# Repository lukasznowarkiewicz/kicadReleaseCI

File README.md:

# KiCad Release CI

This repository provides:

1. A **Docker-based** environment for running [KiCad 8.x](https://www.kicad.org/) in a CI context.  
2. A **reusable GitHub Actions workflow** (`.github/workflows/kicad_export.yml`) that you can call from your PCB project repos.  
3. A **script** that automatically searches for `.kicad_pcb` (and matching `.kicad_sch`) files, exports manufacturing outputs, and stores them in an `outputs/` folder.

## Table of Contents

- [Intended Use](#intended-use)  
- [Using From Another Repository](#using-from-another-repository)  
- [Development](#development)  
  - [1. Build Docker Image Locally](#1-build-docker-image-locally)  
  - [2. Run the Docker Container](#2-run-the-docker-container)  
  - [3. Modify the Export Script](#3-modify-the-export-script)  
- [What is Exported](#what-is-exported)  
- [License](#license)  

---

## Intended Use

- **Automate** KiCad manufacturing outputs (Gerbers, Drill files, BOM, PDF plots, etc.) for your hardware projects.  
- Keep the CI logic and Docker environment **centralized**.  
- **Reusable** across multiple PCB projects.  
- Fully **headless** KiCad environment, leveraging `kicad-cli` commands in KiCad 8.

---

## Using From Another Repository

### 1) Reference Our Reusable Workflow

In your **KiCad project repository**, create a workflow file (e.g., `.github/workflows/kicad_export_caller.yml`):

```yaml
name: "Kicad 8 release CI"

on:
  push:
    branches: [ "main" ]
  pull_request:
    branches: [ "main" ]
  # or to allow manual triggers:
  # workflow_dispatch:

jobs:
  call-export:
    uses: lukasznowarkiewicz/kicadReleaseCI/.github/workflows/kicad_export.yml@main
    with:
      target_repo: ${{ github.repository }}
      target_ref: ${{ github.ref }}
```

- **`uses:`** points to this repo’s workflow file (`kicad_export.yml`).  
- **`target_repo`** and **`target_ref`** are inputs required by the reusable workflow to know which repo and branch to check out.

### 2) Trigger the Workflow

- Whenever you push to `main` or open a pull request, GitHub Actions calls `kicad_export.yml` from **kicadReleaseCI**, checks out your KiCad files, and runs the export container.  
- The results are uploaded as an artifact named `kicad-outputs`. Download it from the “Actions” tab in your project repo.

> **Note**: If your `kicadReleaseCI` repo is **private**, ensure you have set the right permissions and that both repos are in the same organization (or you have a proper token setup).

---

## Development

If you want to **develop** or **modify** this CI workflow in `kicadReleaseCI`, here are common tasks:

### 1. Build Docker Image Locally

```bash
git clone https://github.com/lukasznowarkiewicz/kicadReleaseCI.git
cd kicadReleaseCI
docker build -t kicad-autogen:latest .
```

This uses the local `Dockerfile`, which installs KiCad 8 and copies the `generate_kicad_outputs.sh` script.

### 2. Run the Docker Container

You can run the image manually, mounting a **KiCad project** folder to `/project`:

```bash
docker run --rm -it -v "$(pwd)":/project -w /project kicad-autogen:latest
```

or optinally run container and enter containers' bash:
```bash
docker run --rm -it \
  --entrypoint bash \
  -v "$(pwd)":/project \
  -w /project \
  kicad-autogen:latest
```

- The container entrypoint calls `generate_kicad_outputs.sh`, which searches `/project` for `.kicad_pcb` files, exports all outputs, and places them into `outputs/` subfolders.
- When the container finishes, check `some_kicad_project/outputs/` on your host system for the results.

### 3. Modify the Export Script

- The **main logic** is in `generate_kicad_outputs.sh`. It does:
  - `find . -type f -name '*.kicad_pcb'` to locate boards in subfolders.
  - If a matching `.kicad_sch` is found, exports schematic PDF & BOM.
  - Exports board PDF, Gerbers, and NC drill files for each PCB.
  - Places everything under a mirrored folder structure in `outputs/<subdirectory>`.
- **Common tweaks**:
  - Change PDF layers (default is `F.Cu,B.Cu,F.SilkS,B.SilkS,Edge.Cuts`).
  - Add or remove exports (e.g. `kicad-cli pcb export svg`).
  - Add optional 3D or advanced BOM scripts.

After changes, **rebuild** the Docker image or push to GitHub so the updated script is used in subsequent CI runs.

---

## What is Exported

By default, the script exports the following for each `.kicad_pcb`:

1. **Board PDF**: A multi-layer PDF of copper layers, silkscreen, and board edges.  
2. **Gerber Files**: For each layer, plus `.gbrjob`.  
3. **NC Drill Files**: Excellon drills (`.drl`, `.map`).  
4. **Schematic PDF & BOM**: If a **matching** `.kicad_sch` (same base name) is found. BOM is exported as `.csv`.

All generated files go into `outputs/<mirroring the original folder structure>`. For instance, if your KiCad board is at `sub/folder/myboard.kicad_pcb`, the outputs go to `outputs/sub/folder/`.

---

## License

This project is published under the [Apache-2.0](LICENSE) license.

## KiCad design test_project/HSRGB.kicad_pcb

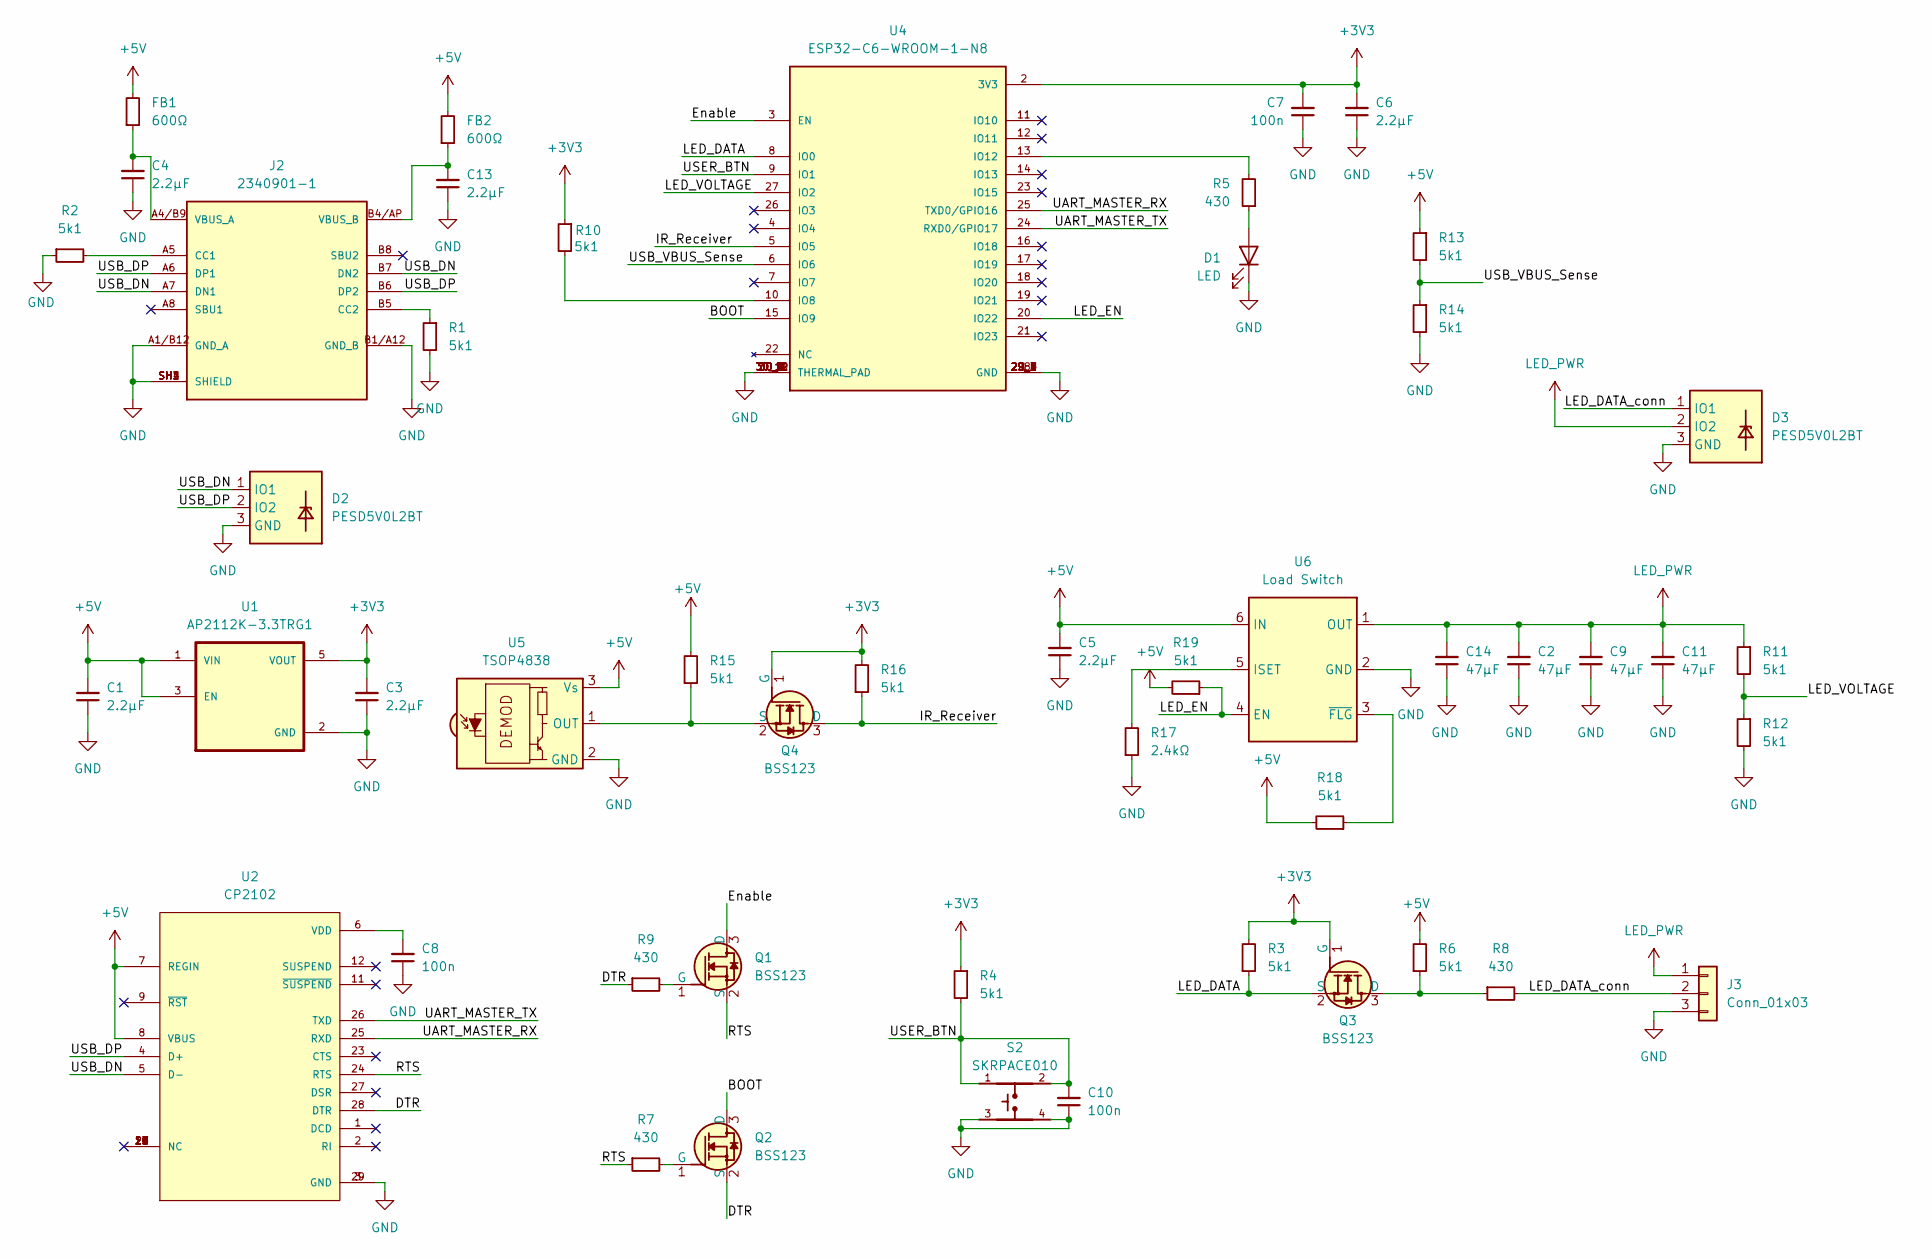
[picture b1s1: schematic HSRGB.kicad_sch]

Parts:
C1, C3, C4, C5, C6, C13: C_2u2_10pct_16V_0402_GRM155R61C225KE11D; C_0402; MPN GRM155R61C225KE11D
C2, C9, C11, C14: C_47u_20pct_10V_0805_CC0805MKX5R6BB476; C_0805; MPN CC0805MKX5R6BB476
C7, C8, C10: C_100n_0402; C_0402; Voltage 10V; MPN GRM155R61A104KE01D
D1: LED; LED_KPT-1608ZGC
D2, D3: PESD5V0L2BT; MPN PESD5V0L2BT
FB1, FB2: FB_600_Ohm_0805; FB_0805_2012Metric; Tolerance ±25%; MPN HCB2012KF-601T15
J2: 2340901-1; PARTREV A
J3: Conn_01x03; 1x03_P2.54mm_LED_pads
Q1, Q2, Q3, Q4: BSS123; SOT-23-3; MPN BSS123
R1, R2, R3, R4, R6, R10, R11, R12, R13, R14, R15, R16, R18, R19: R_5k1_0402; R_0402; Tolerance 5%; MPN AC0402JR-075K1L
R5, R7, R8, R9: R_430_0402; R_0402; Tolerance 1%; MPN RTT024300FTH
R17: R_2k4_1pct_0402_CRCW04022K40FKED; R_0402; MPN CRCW04022K40FKED
S2: SKRPACE010
U1: AP2112K-3.3TRG1; PARTREV 2-2
U2: CP2102
U4: ESP32-C6-WROOM-1-N8; PARTREV 1.0
U5: IR_TSOP4838; Vishay_TSOP4838; MPN TSOP4838
U6: AP22615AWU-7; TSOT-23-6; MPN AP22615AWU-7

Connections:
+3V3: C3.2, C6.2, C7.2, Q3.1 (G), Q4.1 (G), R3.2, R4.1, R10.1, R16.2, U1.5 (VOUT), U4.2 (3V3)
+5V: C1.2, C5.2, FB1.2, FB2.2, R6.2, R13.1, R15.2, R18.2, R19.2, U1.1 (VIN), U1.3 (EN), U2.7 (REGIN), U2.8 (VBUS), U5.3 (Vs), U6.6 (IN)
/BOOT: Q2.3 (D), U4.15 (IO9)
/DTR: Q2.2 (S), R9.1, U2.28 (DTR)
/Enable: Q1.3 (D), U4.3 (EN)
/IR_Receiver: Q4.3 (D), R16.1, U4.5 (IO5)
/LED_DATA: Q3.2 (S), R3.1, U4.8 (IO0)
/LED_DATA_conn: D3.1 (IO1), J3.2, R8.2
/LED_EN: R19.1, U4.20 (IO22), U6.4 (EN)
/LED_VOLTAGE: R11.2, R12.1, U4.27 (IO2)
/RTS: Q1.2 (S), R7.1, U2.24 (RTS)
/UART_MASTER_RX: U2.25 (RXD), U4.25 (TXD0/GPIO16)
/UART_MASTER_TX: U2.26 (TXD), U4.24 (RXD0/GPIO17)
/USB_DN: D2.1 (IO1), J2.A7 (DN1), J2.B7 (DN2), U2.5 (D-)
/USB_DP: D2.2 (IO2), J2.A6 (DP1), J2.B6 (DP2), U2.4 (D+)
/USB_VBUS_Sense: R13.2, R14.1, U4.6 (IO6)
/USER_BTN: C10.2, R4.2, S2.1, S2.2, U4.9 (IO1)
GND: C1.1, C2.1, C3.1, C4.1, C5.1, C6.1, C7.1, C8.1, C9.1, C10.1, C11.1, C13.1, C14.1, D1.1 (K), D2.3 (GND), D3.3 (GND), J2.A1/B12 (GND_A), J2.B1/A12 (GND_B), J2.SH1 (SHIELD), J2.SH2 (SHIELD), J2.SH3 (SHIELD), J2.SH4 (SHIELD), J3.3, R1.2, R2.1, R12.2, R14.2, R17.1, S2.3, S2.4, U1.2 (GND), U2.3 (GND), U2.29 (GND), U4.1 (GND), U4.28 (GND), U4.29_1 (GND), U4.29_2 (GND), U4.29_3 (GND), U4.29_4 (GND), U4.29_5 (GND), U4.29_6 (GND), U4.29_7 (GND), U4.29_8 (GND), U4.29_9 (GND), U4.30_1 (THERMAL_PAD), U4.30_2 (THERMAL_PAD), U4.30_3 (THERMAL_PAD), U4.30_4 (THERMAL_PAD), U4.30_5 (THERMAL_PAD), U4.30_6 (THERMAL_PAD), U4.30_7 (THERMAL_PAD), U4.30_8 (THERMAL_PAD), U4.30_9 (THERMAL_PAD), U4.30_10 (THERMAL_PAD), U4.30_11 (THERMAL_PAD), U4.30_12 (THERMAL_PAD), U5.2 (GND), U6.2 (GND)
LED_PWR: C2.2, C9.2, C11.2, C14.2, D3.2 (IO2), J3.1, R11.1, U6.1 (OUT)
unnamed: D1.2 (A), R5.1
unnamed: J2.A5 (CC1), R2.2
unnamed: J2.B5 (CC2), R1.1
unnamed: C4.2, FB1.1, J2.A4/B9 (VBUS_A)
unnamed: C13.2, FB2.1, J2.B4/AP (VBUS_B)
unnamed: Q1.1 (G), R9.2
unnamed: Q2.1 (G), R7.2
unnamed: Q3.3 (D), R6.1, R8.1
unnamed: Q4.2 (S), R15.1, U5.1 (OUT)
unnamed: C8.2, U2.6 (VDD)
unnamed: R10.2, U4.10 (IO8)
unnamed: R5.2, U4.13 (IO12)
unnamed: R17.2, U6.5 (ISET)
unnamed: R18.1, U6.3 (~FLG)

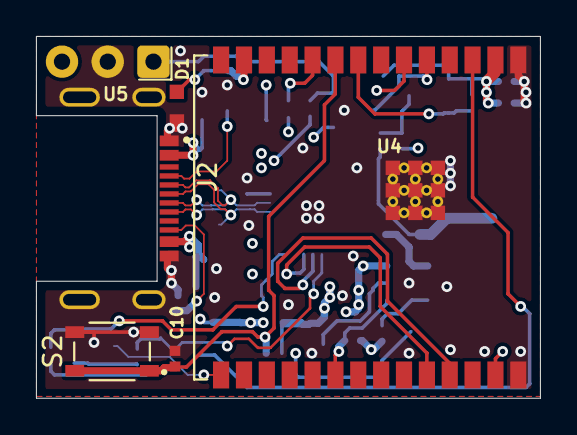
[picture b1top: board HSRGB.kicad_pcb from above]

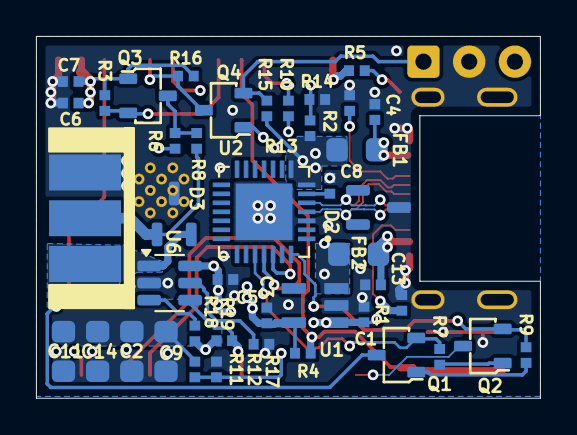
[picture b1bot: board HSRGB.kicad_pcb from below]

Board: 4 copper layers, 28.0 x 20.1 mm, 49 parts (43 on the bottom side), 33 nets.

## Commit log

2025-01-27 Add basic export script and sample project
2025-01-27 Improve schematic export
2025-01-27 Improve BOM export
2025-01-27 Add PCB export to PDF
2025-01-27 Add fabrication export
2025-01-27 Add STEP export
2025-01-28 Create LICENSE
2025-01-28 Update kicad_export.yml name

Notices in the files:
parts and their libraries:
License: Apache-2.0
